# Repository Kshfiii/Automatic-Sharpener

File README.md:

# Da Sharpener
A custom automatic pencil sharpener built around the Seeed Studio XIAO ESP32-C3. It spins an N20 DC motor to sharpen your pencil at the press of a button, and plays Chipi Chipi Chapa Chapa every single time. Because why not.

# About
This is a fully self-contained pencil sharpener with onboard LiPo charging, a boost-converted 6V motor supply, and a DFPlayer Mini for audio playback on a custom 48mm  PCB.
I built this because I wanted to get into PCB design using chips, so that I can confidently use them instead of dev boards in my future projects, all while making something fun and functional. On the hardware side, this project introuced me to audio functions and components.

# Project Snippets

****

# Assembly
To assemble the project open [Onshape](https://cad.onshape.com/documents/c32b9fc8cbec21775e9ce121/w/f4af039bfc6de04a7036ff46/e/f9eacd1e50641cdce73afd8e) In the 'Parts' tab, all parts have been labelled. Now open the Assembly and follow along. Put the assembled PCB between Part 1 and Part 2 and close them together. Put the motor in the rectangle placeholder in Part 2 and cover it with Part 3. After that, Attach Part 3 on the shaft of the motor. attach a sharpner on the underside of Part 4 and then attach Part 4 to Part 3. Lastly, attach Part 6 to the top of Part 3. All of this can be seen in the assembly. If confusion persists, you may contact me at: kasshafemman@gmail.com 

# Usage & Features

  1. Charge via the USB-C port on the XIAO ESP32-C3
  2. Power on using the slide switch
  3. Insert pencil into the sharpener
  4. Hold the tactile switch — motor spins and sharpening begins
  5. Chipi Chipi Chapa Chapa plays through the onboard speaker
  6. Release the switch — motor stops
  7. Take out round cartilage to clean, then insert it back

# Hardware Note — Power Architecture
Attach lipo batter to GND and BATT+ pins on the underside of the Esp32. 

# Firmware Files
Files and their functions:

sharpener.ino — Main loop, switch debounce, motor and audio control
config.h — Pin definitions and settings

# Component List

  1. Seeed Studio XIAO ESP32-C3
  2. TB6612FNG Motor Driver IC
  3. MT3608 Boost Converter IC
  4. AMS1117-5.0 LDO Regulator
  5. N20 DC Gear Motor (6V)
  6. DFPlayer Mini (YX5200)
  7. 8Ω 1W Speaker
  8. Tactile Switch
  9. 3.7V LiPo Battery
  10. MicroSD Card

## Bill of Materials
| Component | Quantity | Est. Cost (USD) | Purchase Links | 
| :--- | :---: | :--- | :--- | 
| **Seeed Studio XIAO ESP32-C**| 1 | $11.50 |[Link](https://www.aliexpress.com/item/1005009855437801.html?spm=a2g0o.detail.0.0.378eYyHPYyHPz5&mp=1&pdp_npi=6%40dis%21USD%21USD%2011.43%21USD%2010.93%21%21USD%2010.93%21%21%21%40212e508f17759555552744763e9213%2112000050381761106%21ct%21PK%21-1%21%211%210%21) | 
| **TB6612FNG Motor Driver IC**| 1 | $1.00 | [Link](https://www.aliexpress.com/item/1005004242795745.html?spm=a2g0o.detail.0.0.35a4meZvmeZvTw&mp=1&pdp_npi=6%40dis%21USD%21USD%201.05%21USD%200.79%21%21USD%200.79%21%21%21%40212e508f17759559005991372e9213%2112000045514972230%21ct%21PK%21-1%21%211%210%21&pdp_ext_f=%7B%22cart2PdpParams%22%3A%7B%22pdpBusinessMode%22%3A%22retail%22%7D%7D) | 
| **MT3608 Boost Converter IC** | 1 | $1.20 | [Link](https://www.aliexpress.com/item/1005008853748359.html?spm=a2g0o.detail.0.0.378eYyHPYyHPz5&mp=1&pdp_npi=6%40dis%21USD%21USD%202.73%21USD%202.23%21%21USD%202.23%21%21%21%40212e508f17759555552744763e9213%2112000046953414150%21ct%21PK%21-1%21%211%210%21) | 
| **AMS1117-5.0 LDO Regulator** | 1 | $2.50 | [Link](https://www.aliexpress.com/item/1005002487704059.html?spm=a2g0o.productlist.main.4.2196rhF6rhF6yu&aem_p4p_detail=20260411180108338023986275640001084750&algo_pvid=16ee6a6a-aaf1-43e2-94e3-907dfa61e2f0&algo_exp_id=16ee6a6a-aaf1-43e2-94e3-907dfa61e2f0-3&pdp_ext_f=%7B%22order%22%3A%223440%22%2C%22eval%22%3A%221%22%2C%22fromPage%22%3A%22search%22%7D&pdp_npi=6%40dis%21USD%212.59%212.09%21%21%212.59%212.09%21%402151e6dc17759556679336660e6cfb%2112000020837902169%21sea%21PK%210%21ABX%211%210%21n_tag%3A-29910%3Bd%3A12fde4ed%3Bm03_new_user%3A-29895%3BpisId%3A5000000203713833&curPageLogUid=jNloBkgONfbe&utparam-url=scene%3Asearch%7Cquery_from%3A%7Cx_object_id%3A1005002487704059%7C_p_origin_prod%3A&search_p4p_id=20260411180108338023986275640001084750_1) | 
| **N20 DC Gear Motor (6V)** | 1 | $2.12 | [Link](https://www.aliexpress.com/item/1005002008404532.html?spm=a2g0o.detail.0.0.4524cmDYcmDYY3&mp=1&pdp_npi=6%40dis%21USD%21USD%202.62%21USD%202.12%21%21USD%202.12%21%21%21%40212e508f17759554877634144e9213%2112000050750804097%21ct%21PK%21-1%21%211%210%21 ) | 
| **MicroSD Card** | 1 | $7.68 | [Link](https://www.aliexpress.com/item/1005007498167692.html?spm=a2g0o.detail.0.0.68ef44ec0VHUwW&mp=1&pdp_npi=6%40dis%21USD%21USD%208.18%21USD%207.68%21%21USD%207.68%21%21%21%40212e508f17759554348433604e9213%2112000041032084439%21ct%21PK%21-1%21%211%210%21) | 
| **8Ω 1W Speaker** | 1 | $1.70 | [Link](https://www.aliexpress.com/item/1005008660223571.html?spm=a2g0o.detail.0.0.173cVO5QVO5QJV&mp=1&pdp_npi=6%40dis%21USD%21USD%204.39%21USD%201.70%21%21USD%201.70%21%21%21%402151e6dc17759543473957645e6ce1%2112000046135720888%21ct%21PK%21-1%21%211%210%21) | 
| **Tactile Switch** | 1 | $0.50 | [Link](https://digilog.pk/products/12-x-12mm-x-7-5mm-push-button-in-pakistan-en?variant=44490991370518 )| 
| **PCB** | 1 | $5.00 | [Link](https://jlcpcb.com/)| 
| **DFPlayer Mini** | 1 | $5.50 | [Link](https://www.aliexpress.com/item/1005011540339952.html?spm=a2g0o.detail.0.0.4b1akxSAkxSANK&mp=1&pdp_npi=6%40dis%21USD%21USD%205.19%21USD%201.99%21%21USD%201.99%21%21%21%40212e520d17760065522677760e7f39%2112000055866842276%21ct%21PK%21-1%21%211%210%21)| 
| **Total Build Cost:** |  | **~$35.00** |

#
Happy Building :)

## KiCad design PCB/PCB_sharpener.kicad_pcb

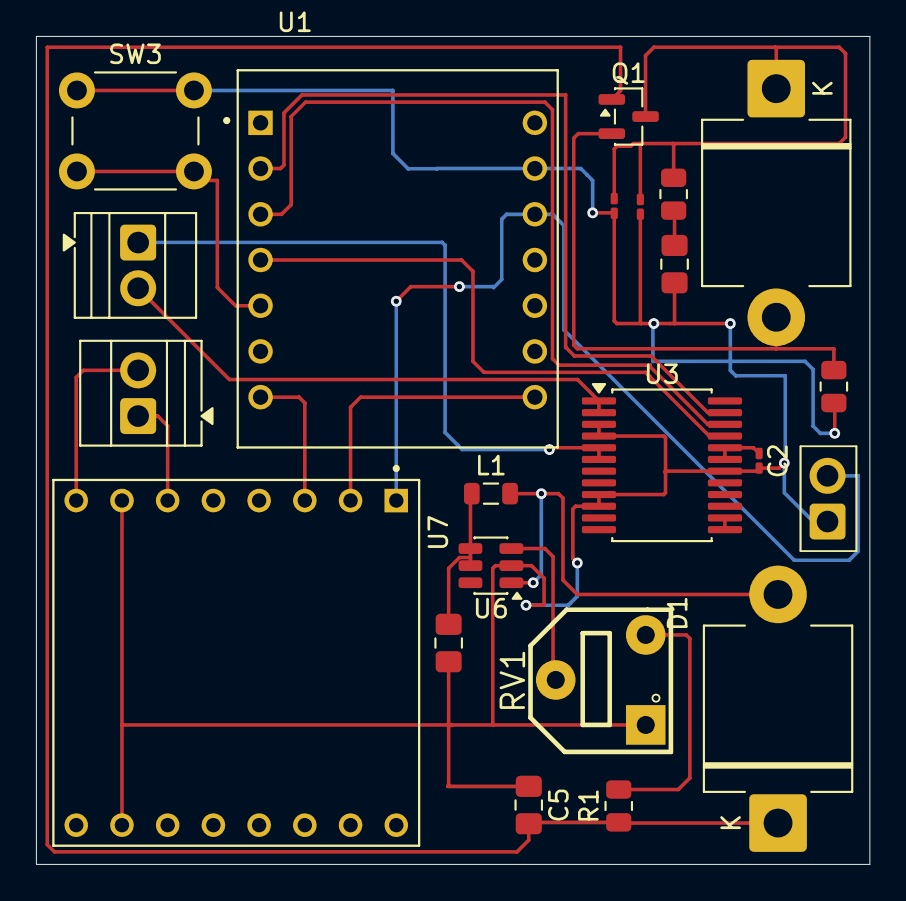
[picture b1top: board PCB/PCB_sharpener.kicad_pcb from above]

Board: 2 copper layers, 46.3 x 46.0 mm, 22 parts (0 on the bottom side), 19 nets.

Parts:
C1, C5: 22uF; C_0805_2012Metric_Pad1.18x1.45mm_HandSolder
C2, C9: 0.1uF; C_0201_0603Metric_Pad0.64x0.40mm_HandSolder
C8: 10uF; C_0805_2012Metric_Pad1.18x1.45mm_HandSolder
C10: 0.47uF; C_0201_0603Metric_Pad0.64x0.40mm_HandSolder
D1: SS34; D_5KPW_P12.70mm_Horizontal
D2: 6.8v; D_5KPW_P12.70mm_Horizontal
J3: Battery; TerminalBlock_Xinya_XY308-2.54-2P_1x02_P2.54mm_Horizontal
J4: Motor; TerminalBlock_Xinya_XY308-2.54-2P_1x02_P2.54mm_Horizontal
J5: Speaker; TerminalBlock_Xinya_XY308-2.54-2P_1x02_P2.54mm_Horizontal
L1: 22µH; L_0805_2012Metric
Q1: AO3401A; SOT-23
R1: 100kΩ; R_0805_2012Metric
R2: 100k; R_0805_2012Metric
R3: 1; R_0805_2012Metric
RV1: 2.2k; MP
SW3: SW_Push; SW_PUSH_6mm_H5mm
U1: XIAO_ESP32C3; MODULE_XIAO_ESP32C3
U3: TB6612FNG; SSOP-24_5.3x8.2mm_P0.65mm
U6: MT3608; SOT-23-6
U7: DFR0299; MODULE_DFR0299

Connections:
3.7v: C1.2, C2.1, J3.2, L1.1, U1.12 (VCC_3V3), U3.19 (STBY), U3.20 (VCC), U6.4 (EN), U6.5 (IN), U7.1 (VCC)
+6V: C5.2, D1.1 (K), Q1.1 (G), R1.1
AIN1: U1.3 (D2), U3.22 (AIN2)
AIN2: U1.4 (D3), U3.21 (AIN1)
AO1: J4.2, U3.1 (AO1), U3.2 (AO1)
AO2: J4.1, U3.5 (AO2), U3.6 (AO2)
GND: C1.1, C2.2, C5.1, C8.2, C9.2, C10.2, J3.1, R2.2, RV1.1, SW3.1, U1.13 (GND), U3.3 (PGND1), U3.4 (PGND1), U3.9 (PGND2), U3.10 (PGND2), U3.18 (GND), U6.2 (GND), U7.7 (GND), U7.10 (GND)
unnamed: C8.1, R3.2
unnamed: D1.2 (A), L1.2, U6.1 (SW)
unnamed: D2.2 (A), Q1.2 (S), R2.1
unnamed: R1.2, RV1.3
unnamed: SW3.2, U1.5 (D4)
unnamed: RV1.2, U6.3 (FB)
PWMA: U1.2 (D1), U3.23 (PWMA)
RX: U1.8 (RX_D7), U7.2 (RX)
SPK1: J5.1, U7.6 (SPK1)
SPK2: J5.2, U7.8 (SPK2)
TX: U1.7 (TX_D6), U7.3 (TX)
VM: C9.1, C10.1, D2.1 (K), Q1.3 (D), R3.1, U3.13 (VM2), U3.14 (VM3), U3.24 (VM1)

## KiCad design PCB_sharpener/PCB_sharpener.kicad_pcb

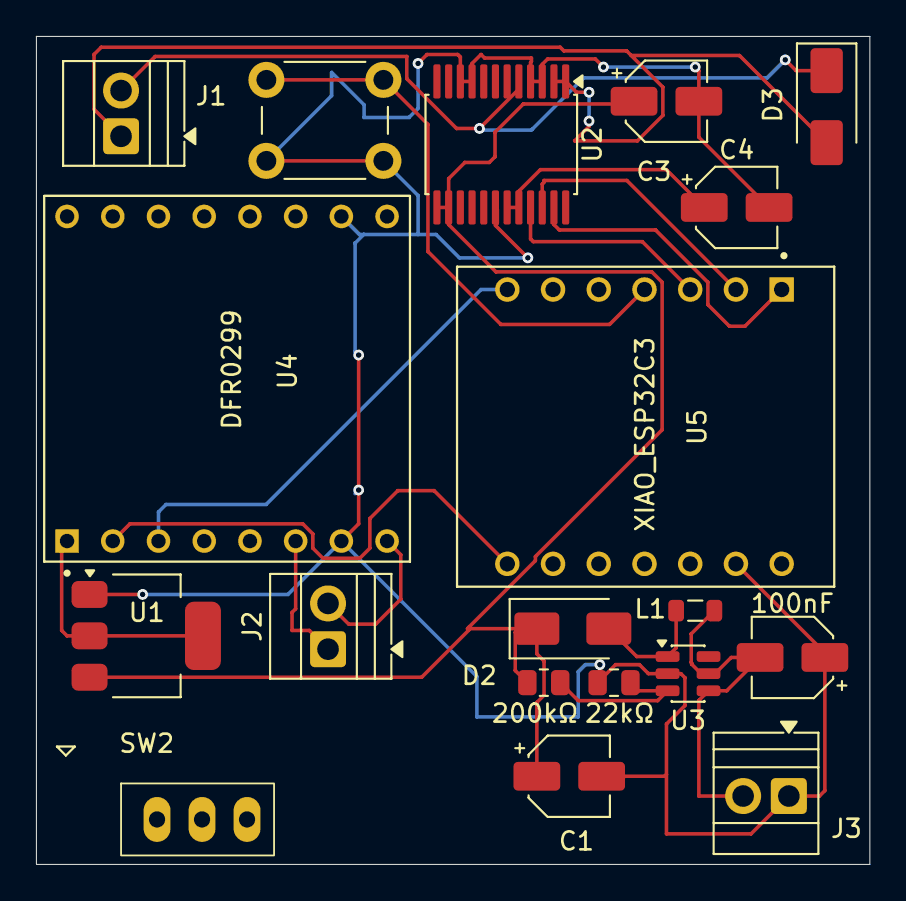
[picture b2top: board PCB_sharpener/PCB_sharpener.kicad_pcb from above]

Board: 2 copper layers, 46.3 x 46.0 mm, 19 parts (0 on the bottom side), 17 nets.

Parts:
C1: 100µF; CP_Elec_4x3
C2: 100nF; CP_Elec_4x3
C3, C4: C; CP_Elec_4x3
D2: D_Schottky; D_SMA
D3: 1N4007; D_SMA
J1, J2, J3: Screw_Terminal_01x02; TerminalBlock_Xinya_XY308-2.54-2P_1x02_P2.54mm_Horizontal
L1: 4.7µH; L_0805_2012Metric
R1: 22kΩ; R_0805_2012Metric
R2: 200kΩ; R_0805_2012Metric
SW1: SW_Push; SW_PUSH_6mm_H5mm
SW2: SW_SPDT; SW_Slide_SP3T_Straight_CK_OS103012MU1QP1
U1: AMS1117-5.0; SOT-223-3_TabPin2
U2: TB6612FNG; SSOP-24_5.3x8.2mm_P0.65mm
U3: MT3608; SOT-23-6
U4: DFR0299; MODULE_DFR0299
U5: XIAO_ESP32C3; MODULE_XIAO_ESP32C3

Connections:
+3.3V: C4.1, U2.19 (STBY), U2.20 (VCC)
+6V: C1.1, C3.1, D2.1 (K), R2.1, U1.3 (VI), U2.13 (VM2), U2.14 (VM3)
+BATT: C2.2, J3.2, L1.1, U3.4 (EN), U3.5 (IN)
GND: C1.2, C2.1, C3.2, C4.2, J3.1, R1.2, SW1.2, U1.1 (GND), U2.3 (PGND1), U2.4 (PGND1), U2.9 (PGND2), U2.10 (PGND2), U2.18 (GND), U3.2 (GND), U4.7 (GND), U4.10 (GND), U5.13 (GND)
unnamed: D2.2 (A), L1.2, U3.1 (SW)
unnamed: D3.2 (A), J1.1, U2.1 (AO1), U2.2 (AO1)
unnamed: D3.1 (K), J1.2, U2.5 (AO2), U2.6 (AO2)
unnamed: J2.1, U4.6 (SPK1)
unnamed: J2.2, U4.8 (SPK2)
unnamed: U1.2 (VO), U4.1 (VCC)
unnamed: U2.21 (AIN1), U5.3 (D2)
unnamed: U2.22 (AIN2), U5.2 (D1)
unnamed: U2.23 (PWMA), U5.1 (D0)
unnamed: R1.1, R2.2, U3.3 (FB)
unnamed: U4.2 (RX), U5.8 (RX_D7)
unnamed: U4.3 (TX), U5.7 (TX_D6)
unnamed: SW1.1, U5.4 (D3)

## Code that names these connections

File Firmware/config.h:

#pragma once

#define PWMA  2
#define AIN1  3
#define AIN2  4
#define BUTTON 5

#define DF_RX 20
#define DF_TX 21

#define MOTOR_SPEED 255
#define DEBOUNCE_MS 50

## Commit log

2026-04-12 Add MIT License to the project
2026-04-13 Update BOM.csv format to standard CSV
2026-04-14 Update project description in README.md
    Removed subtitle from project description.
